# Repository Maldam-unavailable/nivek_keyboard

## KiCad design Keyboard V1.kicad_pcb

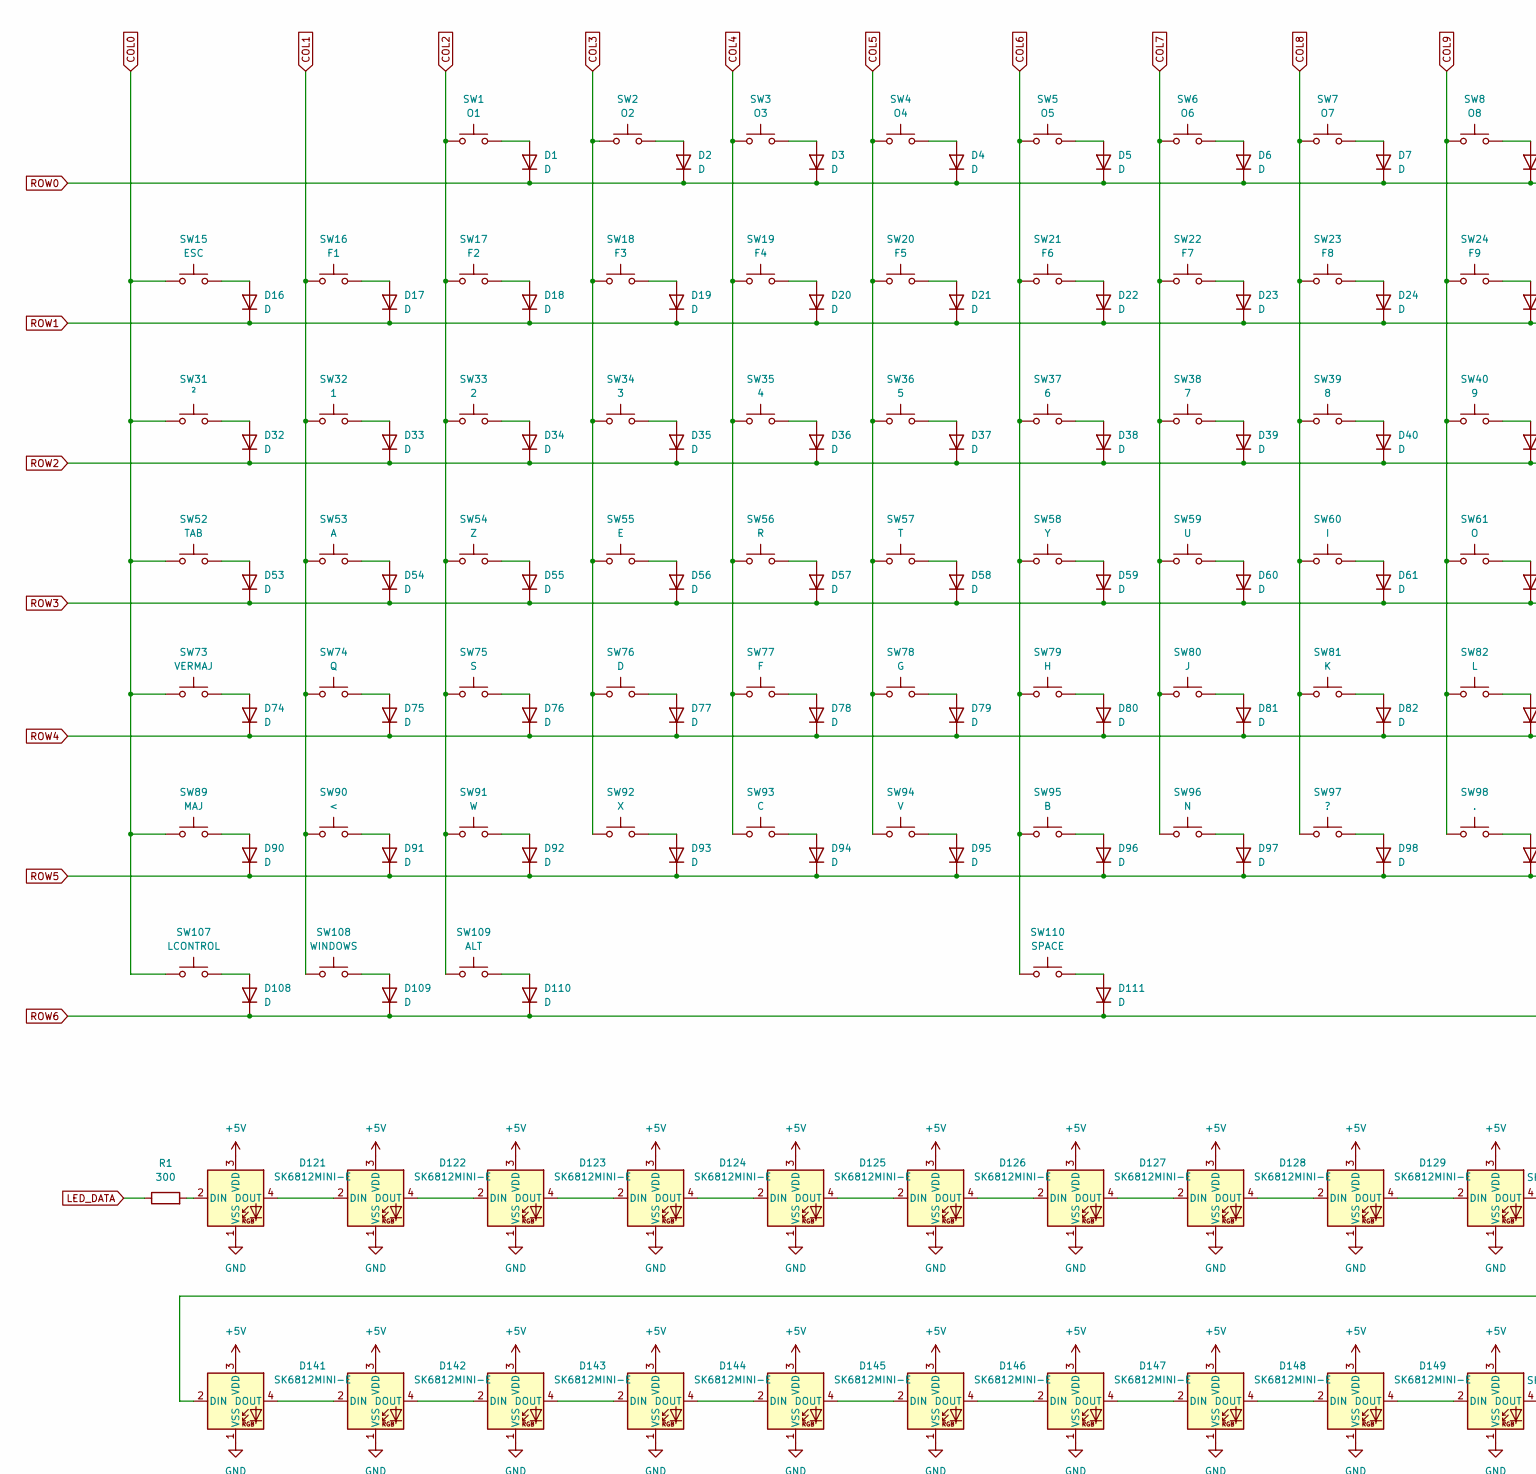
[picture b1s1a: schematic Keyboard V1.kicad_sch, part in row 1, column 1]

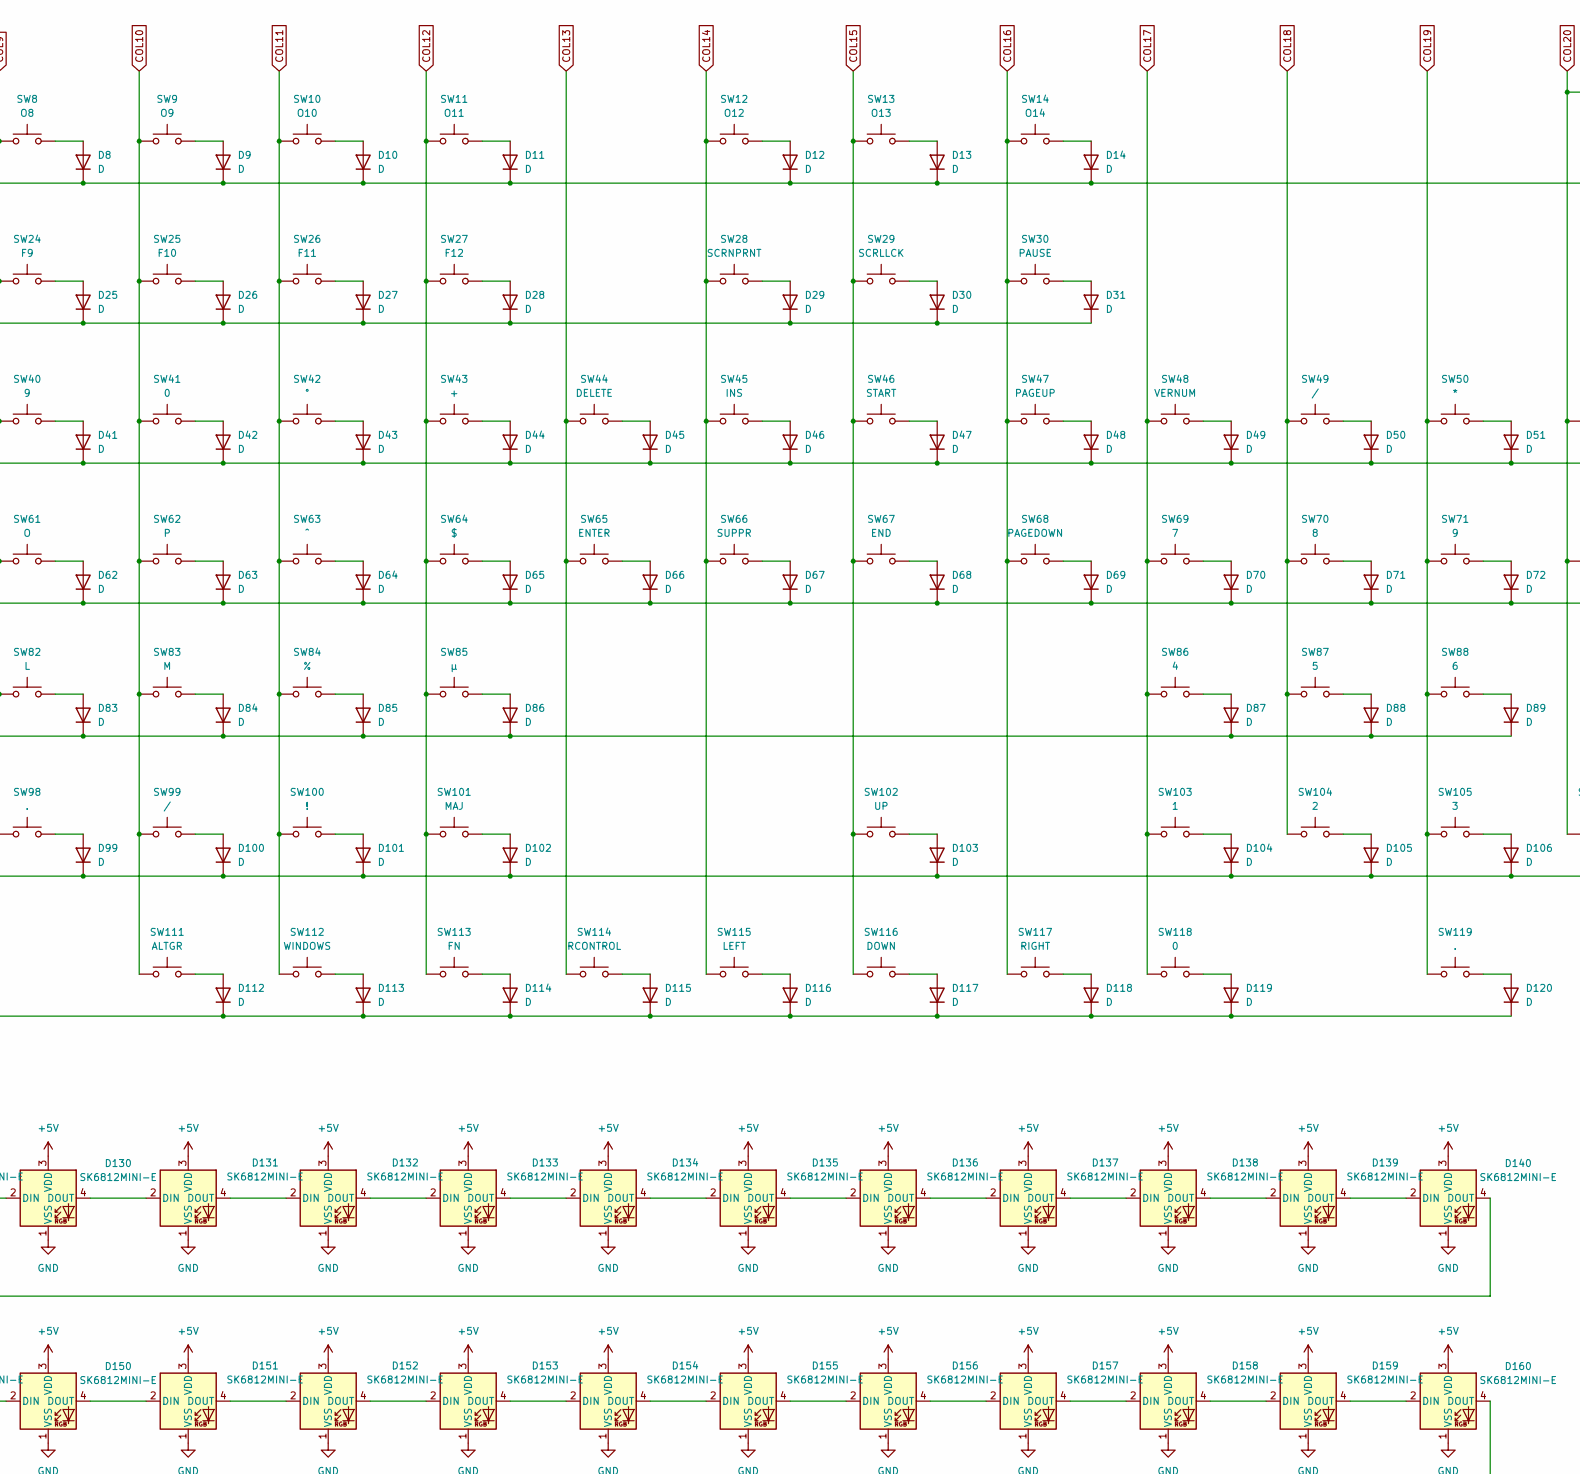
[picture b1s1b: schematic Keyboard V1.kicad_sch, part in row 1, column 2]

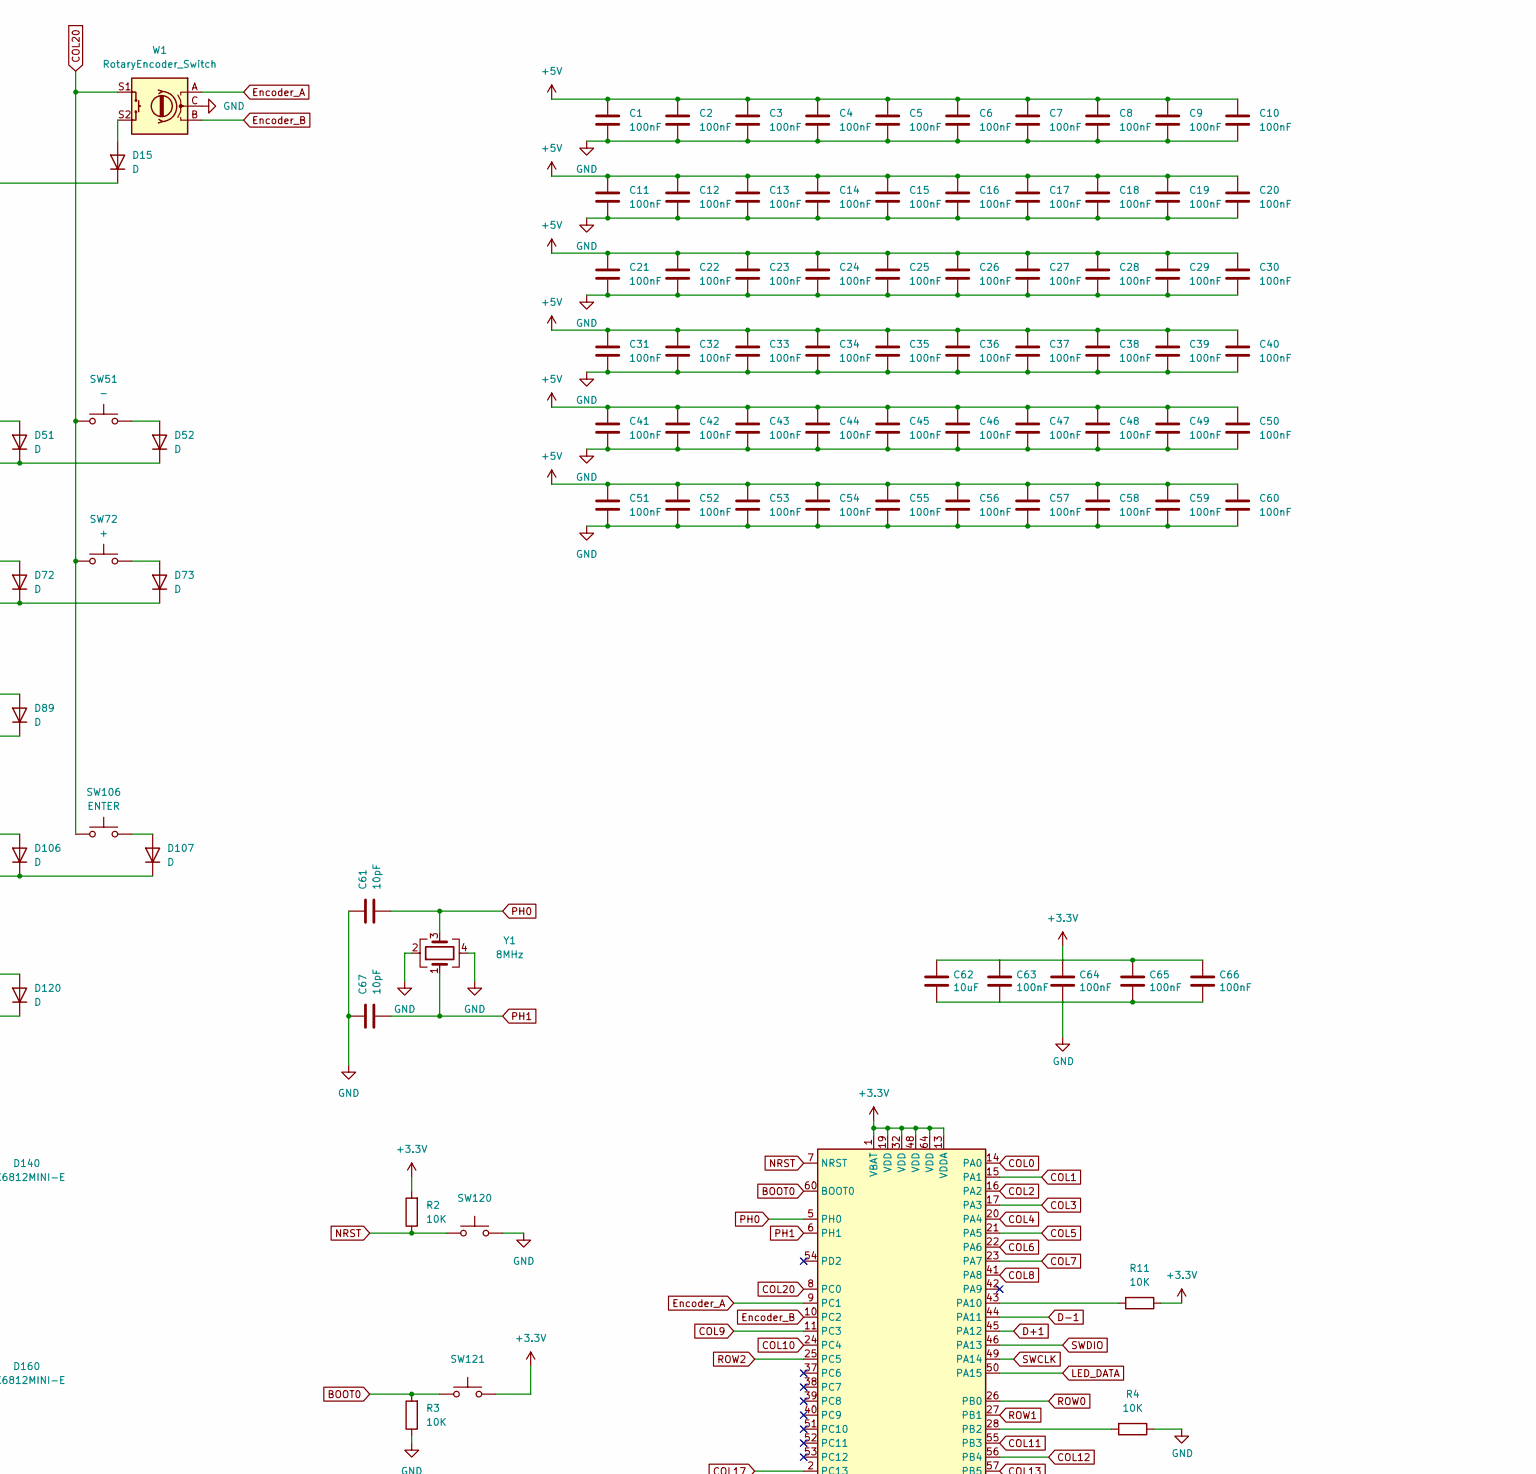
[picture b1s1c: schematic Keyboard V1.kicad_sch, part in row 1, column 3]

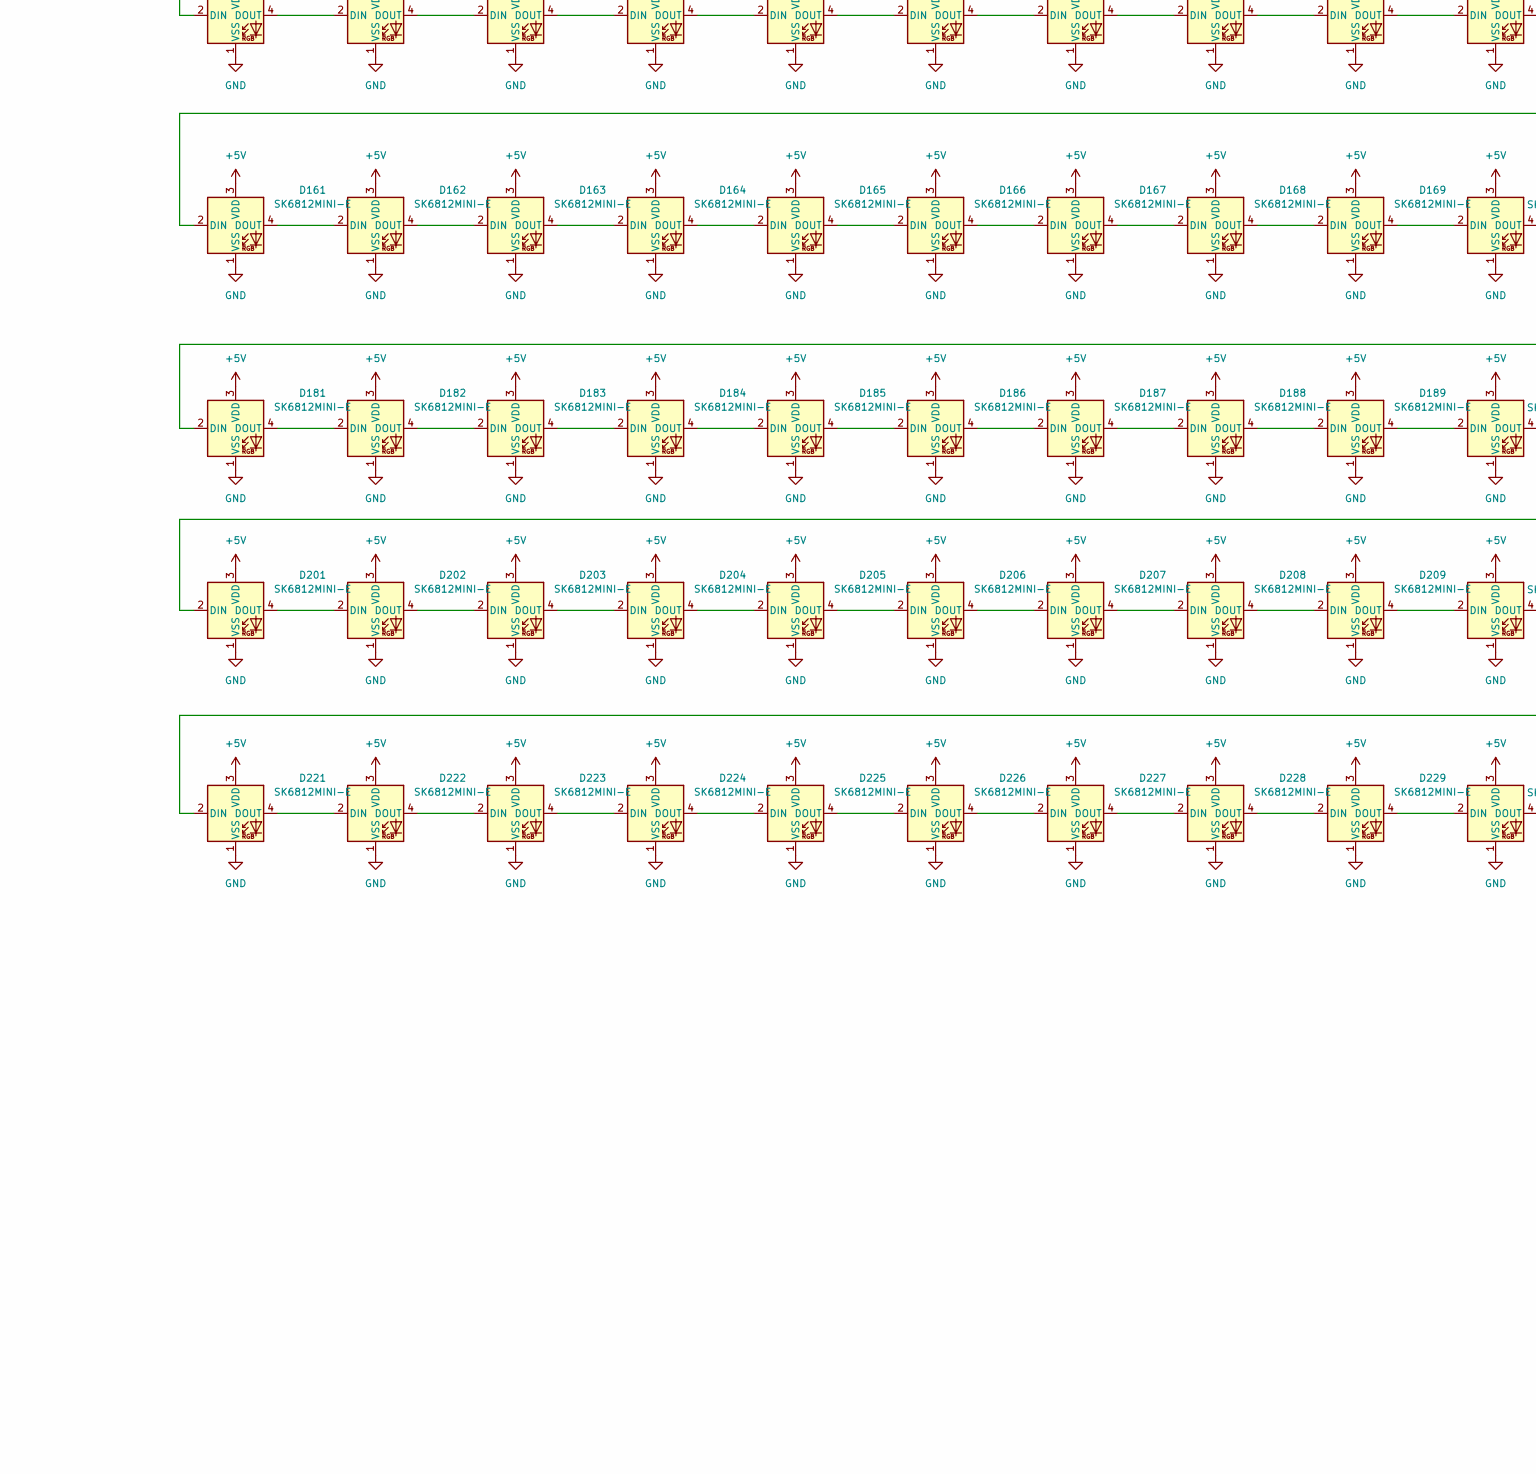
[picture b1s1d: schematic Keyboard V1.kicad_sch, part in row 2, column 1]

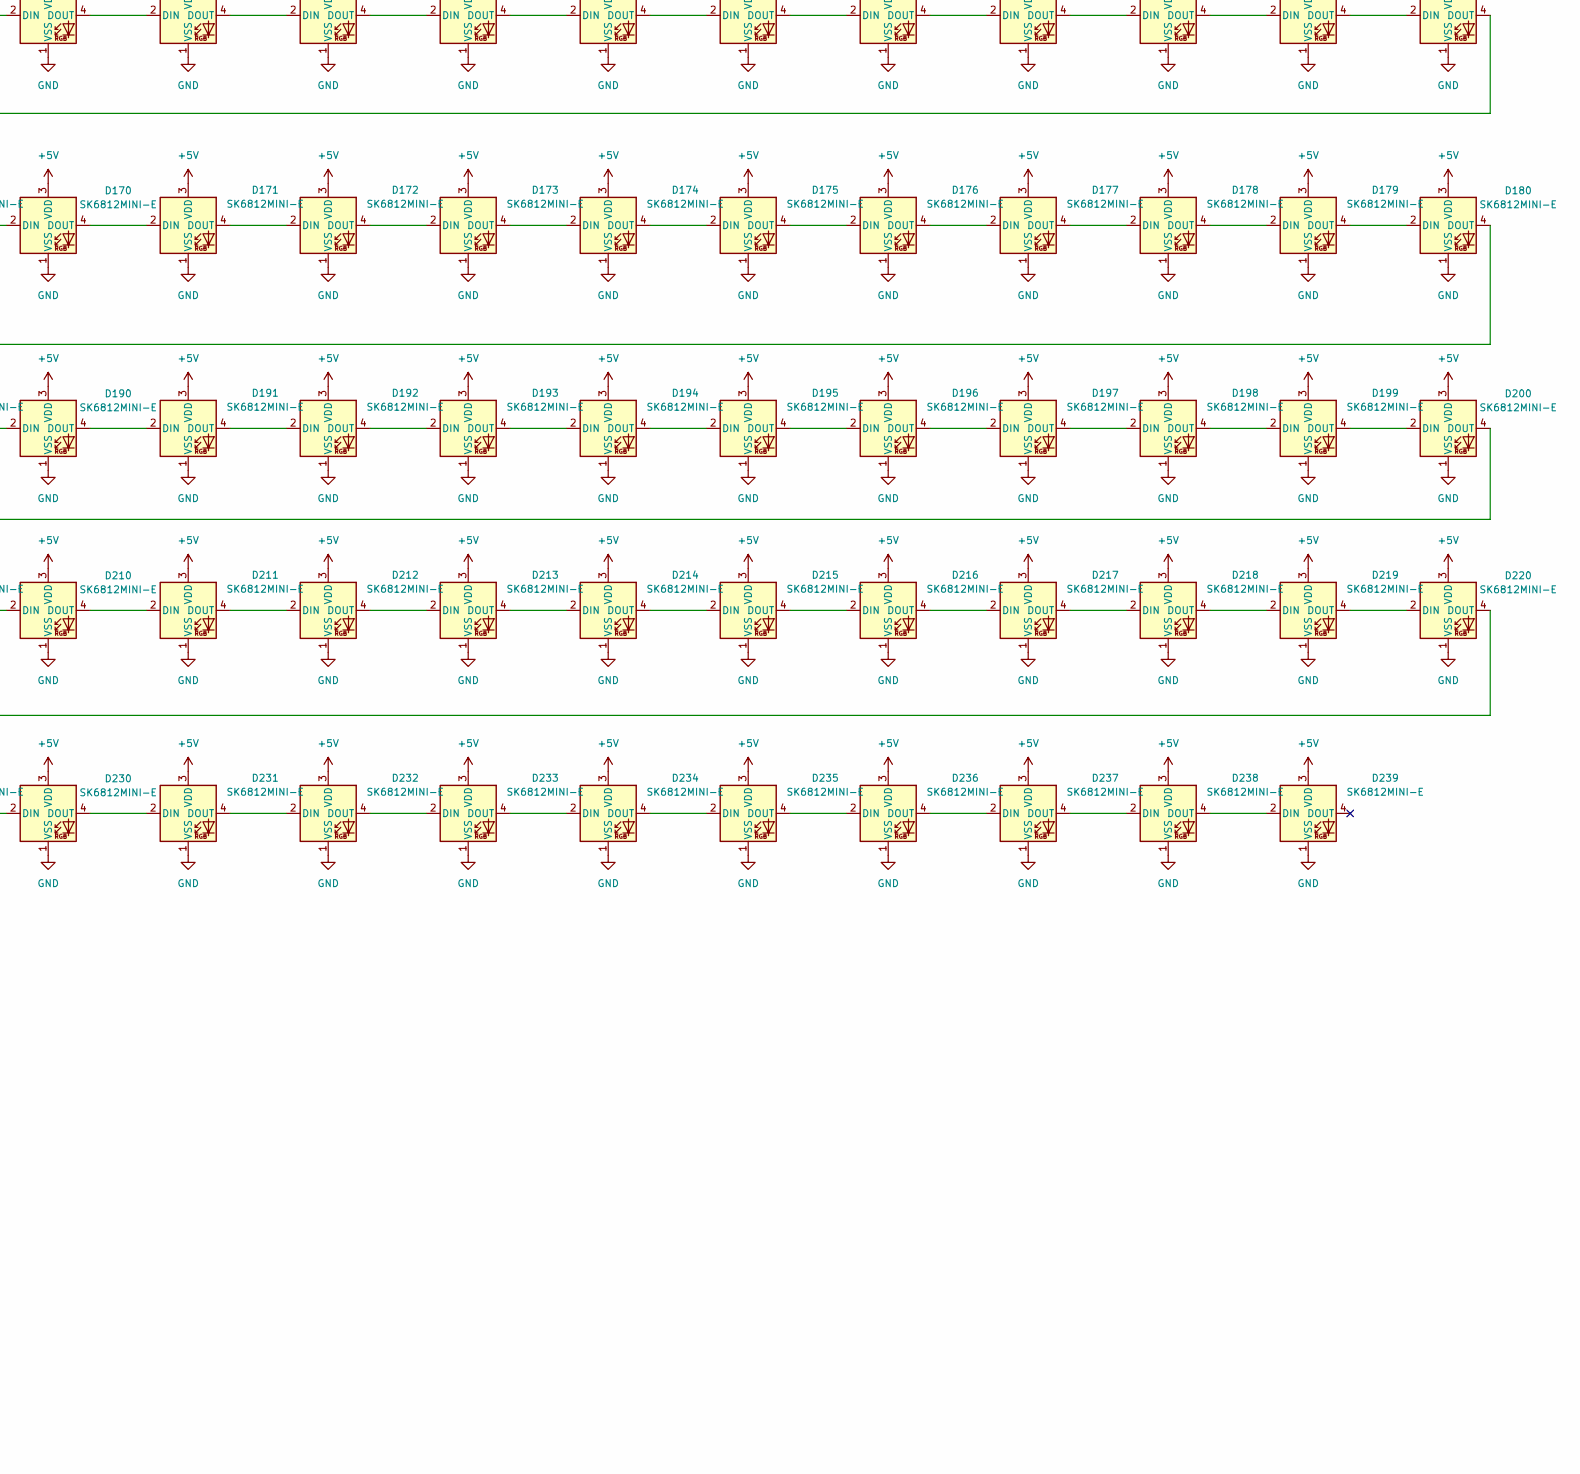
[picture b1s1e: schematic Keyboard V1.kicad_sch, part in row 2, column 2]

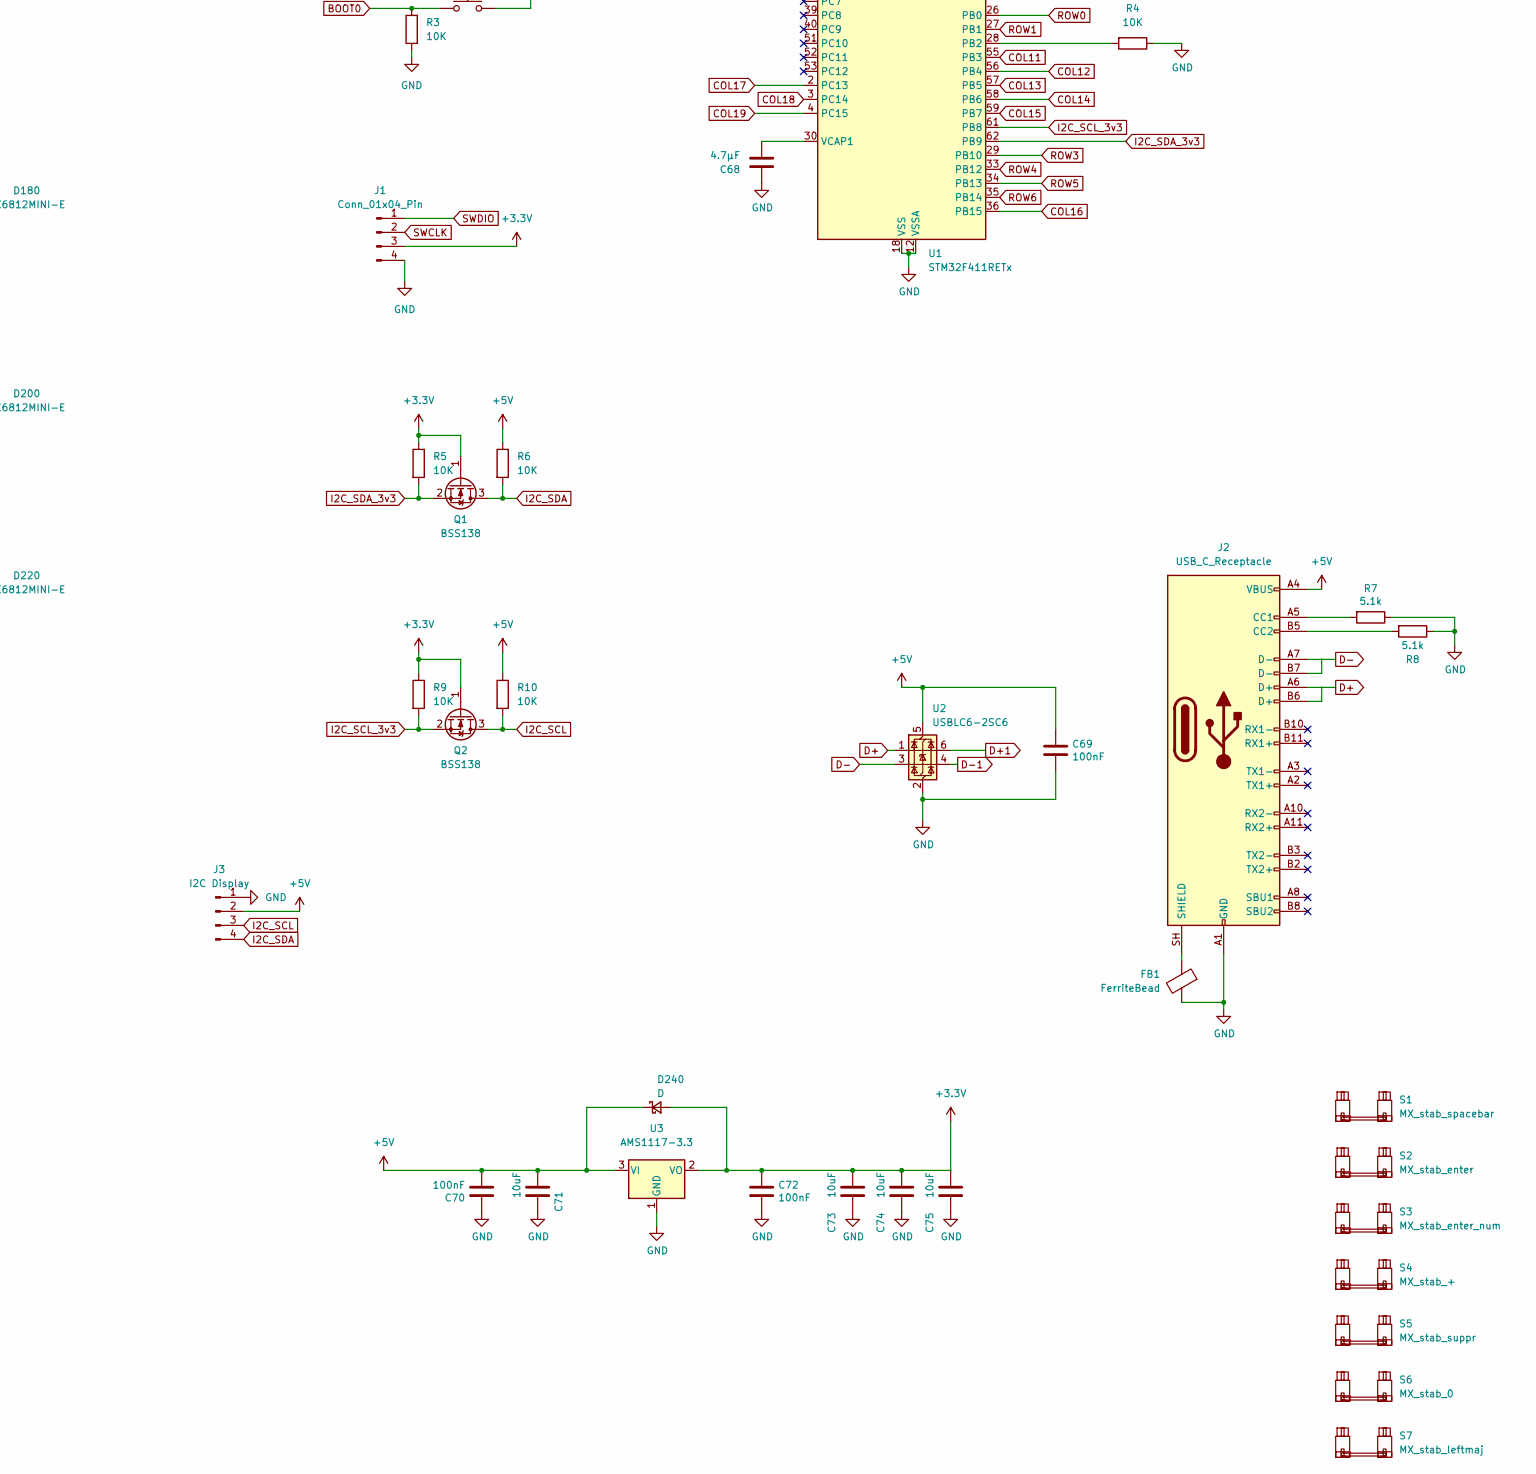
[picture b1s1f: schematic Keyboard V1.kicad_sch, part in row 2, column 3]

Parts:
C1, C2, C3, C4, C5, C6, C7, C8, C9, C10, C11, C12, C13, C14, C15, C16, C17, C18, C19, C20, C21, C22, C23, C24, C25, C26, C27, C28, C29, C30, C31, C32, C33, C34, C35, C36, C37, C38, C39, C40, C41, C42, C43, C44, C45, C46, C47, C48, C49, C50, C51, C52, C53, C54, C55, C56, C57, C58, C59, C60, C63, C64, C65, C66, C69, C70, C72: 100nF; C_0603_1608Metric_Pad1.08x0.95mm_HandSolder
C61, C67: 10pF; C_0603_1608Metric_Pad1.08x0.95mm_HandSolder
C62, C71, C73, C74, C75: 10uF; C_0603_1608Metric_Pad1.08x0.95mm_HandSolder
C68: 4.7µF; C_0603_1608Metric_Pad1.08x0.95mm_HandSolder
D1, D2, D3, D4, D5, D6, D7, D8, D9, D10, D11, D12, D13, D14, D15, D16, D17, D18, D19, D20, D21, D22, D23, D24, D25, D26, D27, D28, D29, D30, D31, D32, D33, D34, D35, D36, D37, D38, D39, D40, D41, D42, D43, D44, D45, D46, D47, D48, D49, D50, D51, D52, D53, D54, D55, D56, D57, D58, D59, D60, D61, D62, D63, D64, D65, D66, D67, D68, D69, D70, D71, D72, D73, D74, D75, D76, D77, D78, D79, D80, D81, D82, D83, D84, D85, D86, D87, D88, D89, D90, D91, D92, D93, D94, D95, D96, D97, D98, D99, D100, D101, D102, D103, D104, D105, D106, D107, D108, D109, D110, D111, D112, D113, D114, D115, D116, D117, D118, D119, D120, D240: D; D_SOD-123F
D121, D122, D123, D124, D125, D126, D127, D128, D129, D130, D131, D132, D133, D134, D135, D136, D137, D138, D139, D140, D141, D142, D143, D144, D145, D146, D147, D148, D149, D150, D151, D152, D153, D154, D155, D156, D157, D158, D159, D160, D161, D162, D163, D164, D165, D166, D167, D168, D169, D170, D171, D172, D173, D174, D175, D176, D177, D178, D179, D180, D181, D182, D183, D184, D185, D186, D187, D188, D189, D190, D191, D192, D193, D194, D195, D196, D197, D198, D199, D200, D201, D202, D203, D204, D205, D206, D207, D208, D209, D210, D211, D212, D213, D214, D215, D216, D217, D218, D219, D220, D221, D222, D223, D224, D225, D226, D227, D228, D229, D230, D231, D232, D233, D234, D235, D236, D237, D238, D239: SK6812MINI-E; LED_SK6812MINI-E_3.2x2.8mm_P1.5mm_ReverseMount
FB1: FerriteBead; C_0805_2012Metric_Pad1.18x1.45mm_HandSolder
J1: Conn_01x04_Pin; PinHeader_1x04_P2.54mm_Vertical
J2: USB_C_Receptacle; USB_C_Receptacle_GCT_USB4085
J3: I2C Display; MODULE_DM-OLED096-636
Q1, Q2: BSS138; SOT-23
R1: 300; R_0402_1005Metric
R2, R3, R4, R5, R6, R9, R10, R11: 10K; R_0603_1608Metric_Pad0.98x0.95mm_HandSolder
R7, R8: 5.1k; R_0603_1608Metric_Pad0.98x0.95mm_HandSolder
S1: MX_stab_spacebar; STAB_MX_P_6.25u
S2: MX_stab_enter; STAB_MX_P_ISO
S3: MX_stab_enter_num; STAB_MX_P_2u
S4: MX_stab_+; STAB_MX_P_2u
S5: MX_stab_suppr; STAB_MX_P_2u
S6: MX_stab_0; STAB_MX_P_2u
S7: MX_stab_leftmaj; STAB_MX_P_2u
SW1: O1; SW_Hotswap_Kailh_MX_1.00u
SW2: O2; SW_Hotswap_Kailh_MX_1.00u
SW3: O3; SW_Hotswap_Kailh_MX_1.00u
SW4: O4; SW_Hotswap_Kailh_MX_1.00u
SW5: O5; SW_Hotswap_Kailh_MX_1.00u
SW6: O6; SW_Hotswap_Kailh_MX_1.00u
SW7: O7; SW_Hotswap_Kailh_MX_1.00u
SW8: O8; SW_Hotswap_Kailh_MX_1.00u
SW9: O9; SW_Hotswap_Kailh_MX_1.00u
SW10: O10; SW_Hotswap_Kailh_MX_1.00u
SW11: O11; SW_Hotswap_Kailh_MX_1.00u
SW12: O12; SW_Hotswap_Kailh_MX_1.00u
SW13: O13; SW_Hotswap_Kailh_MX_1.00u
SW14: O14; SW_Hotswap_Kailh_MX_1.00u
SW15: ESC; SW_Hotswap_Kailh_MX_1.00u
SW16: F1; SW_Hotswap_Kailh_MX_1.00u
SW17: F2; SW_Hotswap_Kailh_MX_1.00u
SW18: F3; SW_Hotswap_Kailh_MX_1.00u
SW19: F4; SW_Hotswap_Kailh_MX_1.00u
SW20: F5; SW_Hotswap_Kailh_MX_1.00u
SW21: F6; SW_Hotswap_Kailh_MX_1.00u
SW22: F7; SW_Hotswap_Kailh_MX_1.00u
SW23: F8; SW_Hotswap_Kailh_MX_1.00u
SW24: F9; SW_Hotswap_Kailh_MX_1.00u
SW25: F10; SW_Hotswap_Kailh_MX_1.00u
SW26: F11; SW_Hotswap_Kailh_MX_1.00u
SW27: F12; SW_Hotswap_Kailh_MX_1.00u
SW28: SCRNPRNT; SW_Hotswap_Kailh_MX_1.00u
SW29: SCRLLCK; SW_Hotswap_Kailh_MX_1.00u
SW30: PAUSE; SW_Hotswap_Kailh_MX_1.00u
SW31: ²; SW_Hotswap_Kailh_MX_1.00u
SW32, SW103: 1; SW_Hotswap_Kailh_MX_1.00u
SW33, SW104: 2; SW_Hotswap_Kailh_MX_1.00u
SW34, SW105: 3; SW_Hotswap_Kailh_MX_1.00u
SW35, SW86: 4; SW_Hotswap_Kailh_MX_1.00u
SW36, SW87: 5; SW_Hotswap_Kailh_MX_1.00u
SW37, SW88: 6; SW_Hotswap_Kailh_MX_1.00u
SW38, SW69: 7; SW_Hotswap_Kailh_MX_1.00u
SW39, SW70: 8; SW_Hotswap_Kailh_MX_1.00u
SW40, SW71: 9; SW_Hotswap_Kailh_MX_1.00u
SW41, SW118: 0; SW_Hotswap_Kailh_MX_1.00u
SW42: °; SW_Hotswap_Kailh_MX_1.00u
SW43: +; SW_Hotswap_Kailh_MX_1.00u
SW44: DELETE; SW_Hotswap_Kailh_MX_2.00u
SW45: INS; SW_Hotswap_Kailh_MX_1.00u
SW46: START; SW_Hotswap_Kailh_MX_1.00u
SW47: PAGEUP; SW_Hotswap_Kailh_MX_1.00u
SW48: VERNUM; SW_Hotswap_Kailh_MX_1.00u
SW49, SW99: /; SW_Hotswap_Kailh_MX_1.00u
SW50: *; SW_Hotswap_Kailh_MX_1.00u
SW51: -; SW_Hotswap_Kailh_MX_1.00u
SW52: TAB; SW_Hotswap_Kailh_MX_1.50u
SW53: A; SW_Hotswap_Kailh_MX_1.00u
SW54: Z; SW_Hotswap_Kailh_MX_1.00u
SW55: E; SW_Hotswap_Kailh_MX_1.00u
SW56: R; SW_Hotswap_Kailh_MX_1.00u
SW57: T; SW_Hotswap_Kailh_MX_1.00u
SW58: Y; SW_Hotswap_Kailh_MX_1.00u
SW59: U; SW_Hotswap_Kailh_MX_1.00u
SW60: I; SW_Hotswap_Kailh_MX_1.00u
SW61: O; SW_Hotswap_Kailh_MX_1.00u
SW62: P; SW_Hotswap_Kailh_MX_1.00u
SW63: ^; SW_Hotswap_Kailh_MX_1.00u
SW64: $; SW_Hotswap_Kailh_MX_1.00u
SW65: ENTER; SW_Hotswap_Kailh_MX_ISOEnter
SW66: SUPPR; SW_Hotswap_Kailh_MX_1.00u
SW67: END; SW_Hotswap_Kailh_MX_1.00u
SW68: PAGEDOWN; SW_Hotswap_Kailh_MX_1.00u
SW72: +; SW_Hotswap_Kailh_MX_2.00u_90deg
SW73: VERMAJ; SW_Hotswap_Kailh_MX_1.75u
SW74: Q; SW_Hotswap_Kailh_MX_1.00u
SW75: S; SW_Hotswap_Kailh_MX_1.00u
SW76: D; SW_Hotswap_Kailh_MX_1.00u
SW77: F; SW_Hotswap_Kailh_MX_1.00u
SW78: G; SW_Hotswap_Kailh_MX_1.00u
SW79: H; SW_Hotswap_Kailh_MX_1.00u
SW80: J; SW_Hotswap_Kailh_MX_1.00u
SW81: K; SW_Hotswap_Kailh_MX_1.00u
SW82: L; SW_Hotswap_Kailh_MX_1.00u
SW83: M; SW_Hotswap_Kailh_MX_1.00u
SW84: %; SW_Hotswap_Kailh_MX_1.00u
SW85: µ; SW_Hotswap_Kailh_MX_1.00u
SW89: MAJ; SW_Hotswap_Kailh_MX_1.25u
SW90: <; SW_Hotswap_Kailh_MX_1.00u
SW91: W; SW_Hotswap_Kailh_MX_1.00u
SW92: X; SW_Hotswap_Kailh_MX_1.00u
SW93: C; SW_Hotswap_Kailh_MX_1.00u
SW94: V; SW_Hotswap_Kailh_MX_1.00u
SW95: B; SW_Hotswap_Kailh_MX_1.00u
SW96: N; SW_Hotswap_Kailh_MX_1.00u
SW97: ?; SW_Hotswap_Kailh_MX_1.00u
SW98, SW119: .; SW_Hotswap_Kailh_MX_1.00u
SW100: !; SW_Hotswap_Kailh_MX_1.00u
SW101: MAJ; SW_Hotswap_Kailh_MX_2.75u
SW102: UP; SW_Hotswap_Kailh_MX_1.00u
SW106: ENTER; SW_Hotswap_Kailh_MX_2.00u_90deg
SW107: LCONTROL; SW_Hotswap_Kailh_MX_1.25u
SW108, SW112: WINDOWS; SW_Hotswap_Kailh_MX_1.25u
SW109: ALT; SW_Hotswap_Kailh_MX_1.25u
SW110: SPACE; SW_Hotswap_Kailh_MX_6.00u
SW111: ALTGR; SW_Hotswap_Kailh_MX_1.25u
SW113: FN; SW_Hotswap_Kailh_MX_1.25u
SW114: RCONTROL; SW_Hotswap_Kailh_MX_1.25u
SW115: LEFT; SW_Hotswap_Kailh_MX_1.00u
SW116: DOWN; SW_Hotswap_Kailh_MX_1.00u
SW117: RIGHT; SW_Hotswap_Kailh_MX_1.00u
SW120, SW121: SW_SPST_Omron_B3FS-100xP
U1: STM32F411RETx; LQFP-64_10x10mm_P0.5mm
U2: USBLC6-2SC6; SOT-23-6
U3: AMS1117-3.3; SOT-223-3_TabPin2
W1: RotaryEncoder_Switch; RotaryEncoder_Alps_EC11E-Switch_Vertical_H20mm
Y1: 8MHz; Oscillator_SMD_Abracon_ASE-4Pin_3.2x2.5mm_HandSoldering

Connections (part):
+3.3V: C62.1, C63.1, C64.1, C65.1, C66.1, C72.1, C73.1, C74.1, C75.1, D240.2 (A), J1.3, Q1.1 (G), Q2.1 (G), R2.2, R5.1, R9.1, R11.1, SW121.2, U1.1 (VBAT), U1.13 (VDDA), U1.19 (VDD), U1.32 (VDD), U1.48 (VDD), U1.64 (VDD), U3.2 (VO)
+5V: C1.1, C2.1, C3.1, C4.1, C5.1, C6.1, C7.1, C8.1, C9.1, C10.1, C11.1, C12.1, C13.1, C14.1, C15.1, C16.1, C17.1, C18.1, C19.1, C20.1, C21.1, C22.1, C23.1, C24.1, C25.1, C26.1, C27.1, C28.1, C29.1, C30.1, C31.1, C32.1, C33.1, C34.1, C35.1, C36.1, C37.1, C38.1, C39.1, C40.1, C41.1, C42.1, C43.1, C44.1, C45.1, C46.1, C47.1, C48.1, C49.1, C50.1, C51.1, C52.1, C53.1, C54.1, C55.1, C56.1, C57.1, C58.1, C59.1, C60.1, C69.1, C70.2, C71.1, D121.3 (VDD), D122.3 (VDD), D123.3 (VDD), D124.3 (VDD), D125.3 (VDD), D126.3 (VDD), D127.3 (VDD), D128.3 (VDD), D129.3 (VDD), D130.3 (VDD), D131.3 (VDD), D132.3 (VDD), D133.3 (VDD), D134.3 (VDD), D135.3 (VDD), D136.3 (VDD), D137.3 (VDD)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
BOOT0: R3.2, SW121.1, U1.60 (BOOT0)
COL0: SW15.1, SW31.1, SW52.1, SW73.1, SW89.1, SW107.1, U1.14 (PA0)
COL1: SW16.1, SW32.1, SW53.1, SW74.1, SW90.1, SW108.1, U1.15 (PA1)
COL2: SW1.1, SW17.1, SW33.1, SW54.1, SW75.1, SW91.1, SW109.1, U1.16 (PA2)
COL3: SW2.1, SW18.1, SW34.1, SW55.1, SW76.1, SW92.1, U1.17 (PA3)
COL4: SW3.1, SW19.1, SW35.1, SW56.1, SW77.1, SW93.1, U1.20 (PA4)
COL5: SW4.1, SW20.1, SW36.1, SW57.1, SW78.1, SW94.1, U1.21 (PA5)
COL6: SW5.1, SW21.1, SW37.1, SW58.1, SW79.1, SW95.1, SW110.1, U1.22 (PA6)
COL7: SW6.1, SW22.1, SW38.1, SW59.1, SW80.1, SW96.1, U1.23 (PA7)
COL8: SW7.1, SW23.1, SW39.1, SW60.1, SW81.1, SW97.1, U1.41 (PA8)
COL9: SW8.1, SW24.1, SW40.1, SW61.1, SW82.1, SW98.1, U1.11 (PC3)
COL10: SW9.1, SW25.1, SW41.1, SW62.1, SW83.1, SW99.1, SW111.1, U1.24 (PC4)
COL11: SW10.1, SW26.1, SW42.1, SW63.1, SW84.1, SW100.1, SW112.1, U1.55 (PB3)
COL12: SW11.1, SW27.1, SW43.1, SW64.1, SW85.1, SW101.1, SW113.1, U1.56 (PB4)
COL13: SW44.1, SW65.1, SW114.1, U1.57 (PB5)
COL14: SW12.1, SW28.1, SW45.1, SW66.1, SW115.1, U1.58 (PB6)
COL15: SW13.1, SW29.1, SW46.1, SW67.1, SW102.1, SW116.1, U1.59 (PB7)
COL16: SW14.1, SW30.1, SW47.1, SW68.1, SW117.1, U1.36 (PB15)
COL17: SW48.1, SW69.1, SW86.1, SW103.1, SW118.1, U1.2 (PC13)
COL18: SW49.1, SW70.1, SW87.1, SW104.1, U1.3 (PC14)
COL19: SW50.1, SW71.1, SW88.1, SW105.1, SW119.1, U1.4 (PC15)
COL20: SW51.1, SW72.1, SW106.1, U1.8 (PC0), W1.S1
D+: J2.A6 (D+), J2.B6 (D+), U2.1 (I/O1)
D+1: U1.45 (PA12), U2.6 (I/O1)
D-: J2.A7 (D-), J2.B7 (D-), U2.3 (I/O2)
D-1: U1.44 (PA11), U2.4 (I/O2)
Encoder_A: U1.9 (PC1), W1.A
Encoder_B: U1.10 (PC2), W1.B
GND: C1.2, C2.2, C3.2, C4.2, C5.2, C6.2, C7.2, C8.2, C9.2, C10.2, C11.2, C12.2, C13.2, C14.2, C15.2, C16.2, C17.2, C18.2, C19.2, C20.2, C21.2, C22.2, C23.2, C24.2, C25.2, C26.2, C27.2, C28.2, C29.2, C30.2, C31.2, C32.2, C33.2, C34.2, C35.2, C36.2, C37.2, C38.2, C39.2, C40.2, C41.2, C42.2, C43.2, C44.2, C45.2, C46.2, C47.2, C48.2, C49.2, C50.2, C51.2, C52.2, C53.2, C54.2, C55.2, C56.2, C57.2, C58.2, C59.2, C60.2, C61.1, C62.2, C63.2, C64.2, C65.2, C66.2, C67.1, C68.1, C69.2, C70.1, C71.2, C72.2, C73.2, C74.2, C75.2, D121.1 (VSS), D122.1 (VSS), D123.1 (VSS), D124.1 (VSS), D125.1 (VSS)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
I2C_SCL: J3.3, Q2.3 (D), R10.2
I2C_SCL_3v3: Q2.2 (S), R9.2, U1.61 (PB8)
I2C_SDA: J3.4, Q1.3 (D), R6.2
I2C_SDA_3v3: Q1.2 (S), R5.2, U1.62 (PB9)
LED_DATA: R1.1, U1.50 (PA15)
NRST: R2.1, SW120.1, U1.7 (NRST)
unnamed: D1.2 (A), SW1.2
unnamed: D2.2 (A), SW2.2
unnamed: D3.2 (A), SW3.2
unnamed: D4.2 (A), SW4.2
unnamed: D5.2 (A), SW5.2
unnamed: D6.2 (A), SW6.2
unnamed: D7.2 (A), SW7.2
unnamed: D8.2 (A), SW8.2
unnamed: D9.2 (A), SW9.2
unnamed: D10.2 (A), SW10.2
unnamed: D11.2 (A), SW11.2
unnamed: D12.2 (A), SW12.2
unnamed: D13.2 (A), SW13.2
unnamed: D14.2 (A), SW14.2
unnamed: D15.2 (A), W1.S2
unnamed: D16.2 (A), SW15.2
unnamed: D17.2 (A), SW16.2
unnamed: D18.2 (A), SW17.2
unnamed: D19.2 (A), SW18.2
unnamed: D20.2 (A), SW19.2
unnamed: D21.2 (A), SW20.2
unnamed: D22.2 (A), SW21.2
unnamed: D23.2 (A), SW22.2
unnamed: D24.2 (A), SW23.2
unnamed: D25.2 (A), SW24.2
unnamed: D26.2 (A), SW25.2
unnamed: D27.2 (A), SW26.2
unnamed: D28.2 (A), SW27.2
unnamed: D29.2 (A), SW28.2
unnamed: D30.2 (A), SW29.2
unnamed: D31.2 (A), SW30.2
unnamed: D32.2 (A), SW31.2
unnamed: D33.2 (A), SW32.2
unnamed: D34.2 (A), SW33.2
unnamed: D35.2 (A), SW34.2
unnamed: D36.2 (A), SW35.2
unnamed: D37.2 (A), SW36.2
unnamed: D38.2 (A), SW37.2
unnamed: D39.2 (A), SW38.2
unnamed: D40.2 (A), SW39.2
unnamed: D41.2 (A), SW40.2
unnamed: D42.2 (A), SW41.2
unnamed: D43.2 (A), SW42.2
unnamed: D44.2 (A), SW43.2
unnamed: D45.2 (A), SW44.2
unnamed: D46.2 (A), SW45.2
unnamed: D47.2 (A), SW46.2
unnamed: D48.2 (A), SW47.2
unnamed: D49.2 (A), SW48.2
unnamed: D50.2 (A), SW49.2
unnamed: D51.2 (A), SW50.2
unnamed: D52.2 (A), SW51.2
unnamed: D53.2 (A), SW52.2
unnamed: D54.2 (A), SW53.2
unnamed: D55.2 (A), SW54.2
unnamed: D56.2 (A), SW55.2
unnamed: D57.2 (A), SW56.2
unnamed: D58.2 (A), SW57.2
unnamed: D59.2 (A), SW58.2
unnamed: D60.2 (A), SW59.2
unnamed: D61.2 (A), SW60.2
unnamed: D62.2 (A), SW61.2
unnamed: D63.2 (A), SW62.2
unnamed: D64.2 (A), SW63.2
unnamed: D65.2 (A), SW64.2
unnamed: D66.2 (A), SW65.2
unnamed: D67.2 (A), SW66.2
unnamed: D68.2 (A), SW67.2
unnamed: D69.2 (A), SW68.2
unnamed: D70.2 (A), SW69.2
unnamed: D71.2 (A), SW70.2
unnamed: D72.2 (A), SW71.2
unnamed: D73.2 (A), SW72.2
unnamed: D74.2 (A), SW73.2
unnamed: D75.2 (A), SW74.2
unnamed: D76.2 (A), SW75.2
unnamed: D77.2 (A), SW76.2
unnamed: D78.2 (A), SW77.2
unnamed: D79.2 (A), SW78.2
unnamed: D80.2 (A), SW79.2
unnamed: D81.2 (A), SW80.2
unnamed: D82.2 (A), SW81.2
unnamed: D83.2 (A), SW82.2
unnamed: D84.2 (A), SW83.2
unnamed: D85.2 (A), SW84.2
unnamed: D86.2 (A), SW85.2
unnamed: D87.2 (A), SW86.2
unnamed: D88.2 (A), SW87.2
unnamed: D89.2 (A), SW88.2
unnamed: D90.2 (A), SW89.2
unnamed: D91.2 (A), SW90.2
unnamed: D92.2 (A), SW91.2
unnamed: D93.2 (A), SW92.2
unnamed: D94.2 (A), SW93.2
unnamed: D95.2 (A), SW94.2
unnamed: D96.2 (A), SW95.2
unnamed: D97.2 (A), SW96.2
unnamed: D98.2 (A), SW97.2
unnamed: D99.2 (A), SW98.2
unnamed: D100.2 (A), SW99.2
unnamed: D101.2 (A), SW100.2
unnamed: D102.2 (A), SW101.2
unnamed: D103.2 (A), SW102.2
unnamed: D104.2 (A), SW103.2
unnamed: D105.2 (A), SW104.2
unnamed: D106.2 (A), SW105.2
unnamed: D107.2 (A), SW106.2
unnamed: D108.2 (A), SW107.2
unnamed: D109.2 (A), SW108.2
unnamed: D110.2 (A), SW109.2
unnamed: D111.2 (A), SW110.2
unnamed: D112.2 (A), SW111.2
unnamed: D113.2 (A), SW112.2
unnamed: D114.2 (A), SW113.2
unnamed: D115.2 (A), SW114.2
unnamed: D116.2 (A), SW115.2
unnamed: D117.2 (A), SW116.2
unnamed: D118.2 (A), SW117.2
unnamed: D119.2 (A), SW118.2
unnamed: D120.2 (A), SW119.2
unnamed: D121.2 (DIN), R1.2
unnamed: D121.4 (DOUT), D122.2 (DIN)
unnamed: D122.4 (DOUT), D123.2 (DIN)
unnamed: D123.4 (DOUT), D124.2 (DIN)
unnamed: D124.4 (DOUT), D125.2 (DIN)
unnamed: D125.4 (DOUT), D126.2 (DIN)
unnamed: D126.4 (DOUT), D127.2 (DIN)
unnamed: D127.4 (DOUT), D128.2 (DIN)
unnamed: D128.4 (DOUT), D129.2 (DIN)
unnamed: D129.4 (DOUT), D130.2 (DIN)
unnamed: D130.4 (DOUT), D131.2 (DIN)
unnamed: D131.4 (DOUT), D132.2 (DIN)
unnamed: D132.4 (DOUT), D133.2 (DIN)
unnamed: D133.4 (DOUT), D134.2 (DIN)
unnamed: D134.4 (DOUT), D135.2 (DIN)
unnamed: D135.4 (DOUT), D136.2 (DIN)
unnamed: D136.4 (DOUT), D137.2 (DIN)
unnamed: D137.4 (DOUT), D138.2 (DIN)
unnamed: D138.4 (DOUT), D139.2 (DIN)
unnamed: D139.4 (DOUT), D140.2 (DIN)
unnamed: D140.4 (DOUT), D141.2 (DIN)
unnamed: D141.4 (DOUT), D142.2 (DIN)
unnamed: D142.4 (DOUT), D143.2 (DIN)
unnamed: D143.4 (DOUT), D144.2 (DIN)
unnamed: D144.4 (DOUT), D145.2 (DIN)
unnamed: D145.4 (DOUT), D146.2 (DIN)
unnamed: D146.4 (DOUT), D147.2 (DIN)
unnamed: D147.4 (DOUT), D148.2 (DIN)
unnamed: D148.4 (DOUT), D149.2 (DIN)
unnamed: D149.4 (DOUT), D150.2 (DIN)
unnamed: D150.4 (DOUT), D151.2 (DIN)
unnamed: D151.4 (DOUT), D152.2 (DIN)
unnamed: D152.4 (DOUT), D153.2 (DIN)
unnamed: D153.4 (DOUT), D154.2 (DIN)
unnamed: D154.4 (DOUT), D155.2 (DIN)
unnamed: D155.4 (DOUT), D156.2 (DIN)
unnamed: D156.4 (DOUT), D157.2 (DIN)
unnamed: D157.4 (DOUT), D158.2 (DIN)
unnamed: D158.4 (DOUT), D159.2 (DIN)
unnamed: D159.4 (DOUT), D160.2 (DIN)
unnamed: D160.4 (DOUT), D161.2 (DIN)
unnamed: D161.4 (DOUT), D162.2 (DIN)
unnamed: D162.4 (DOUT), D163.2 (DIN)
unnamed: D163.4 (DOUT), D164.2 (DIN)
unnamed: D164.4 (DOUT), D165.2 (DIN)
unnamed: D165.4 (DOUT), D166.2 (DIN)
unnamed: D166.4 (DOUT), D167.2 (DIN)
unnamed: D167.4 (DOUT), D168.2 (DIN)
unnamed: D168.4 (DOUT), D169.2 (DIN)
unnamed: D169.4 (DOUT), D170.2 (DIN)
unnamed: D170.4 (DOUT), D171.2 (DIN)
unnamed: D171.4 (DOUT), D172.2 (DIN)
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
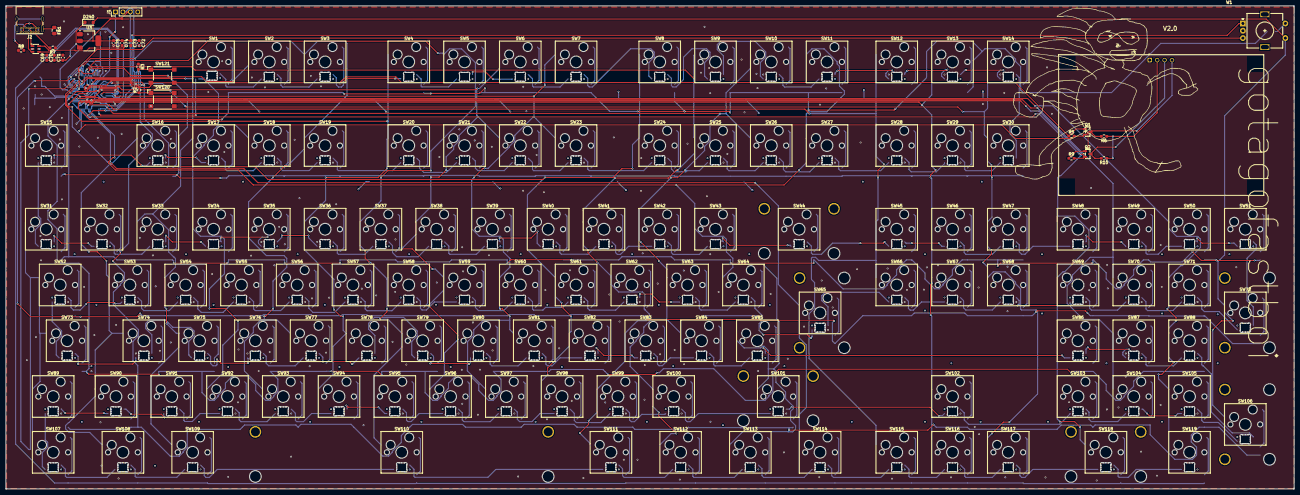
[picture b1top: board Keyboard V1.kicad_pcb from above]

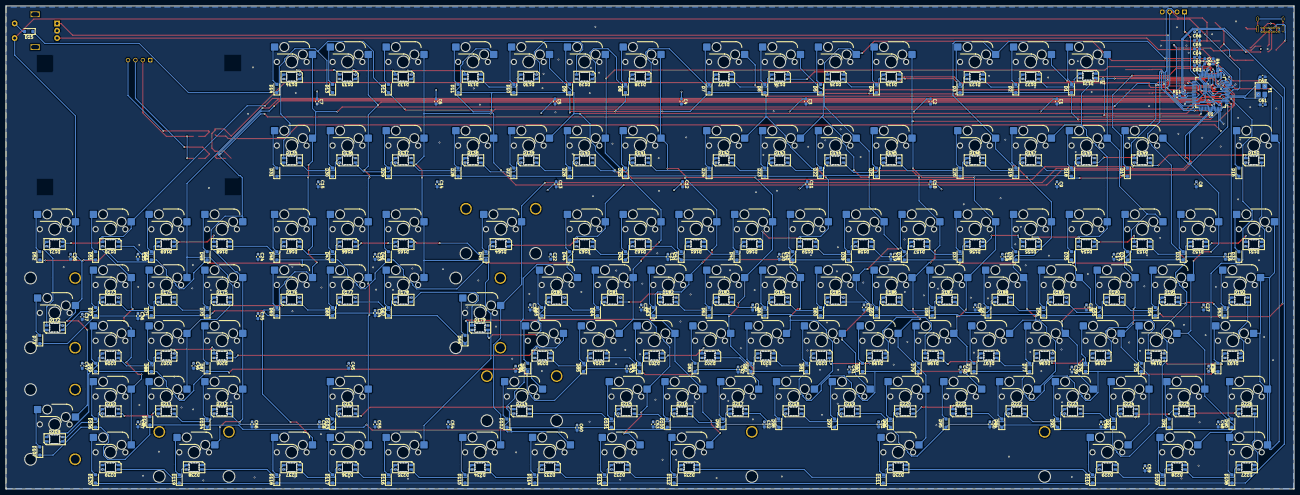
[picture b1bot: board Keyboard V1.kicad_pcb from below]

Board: 4 copper layers, 440.0 x 165.0 mm, 466 parts (312 on the bottom side), 293 nets.

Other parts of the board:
gotagofasboii: LOGO
